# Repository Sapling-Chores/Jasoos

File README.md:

<div align = "center">

# Jasoos

</div>

This is compact keychain voice recorder (~~Not a Spy Gadget~~). This project uses an esp32 s3 with a sd card slot and a cam module that I wish to use in the upgraded version of this project. This project uses an INMP441 to record very good quality audio. Most interestingly, to on the device you have to enter a certain morse using tactile button. This project also uses a sleep mechanism that you can set in the code.

## Why I made this project?

I am a very big fan of crime documentories and shows that forces you to think. So I always thought, what can I do in a situation like a threat or a fight or an argument that could get you in trouble later. And yeah its simple just carry a voice recorder (for ethical use only) that can record audio whenever you want.

## Schematics:

## PCB:

# Cad

Snap fit cross section:

Snap fit female

snap fit male

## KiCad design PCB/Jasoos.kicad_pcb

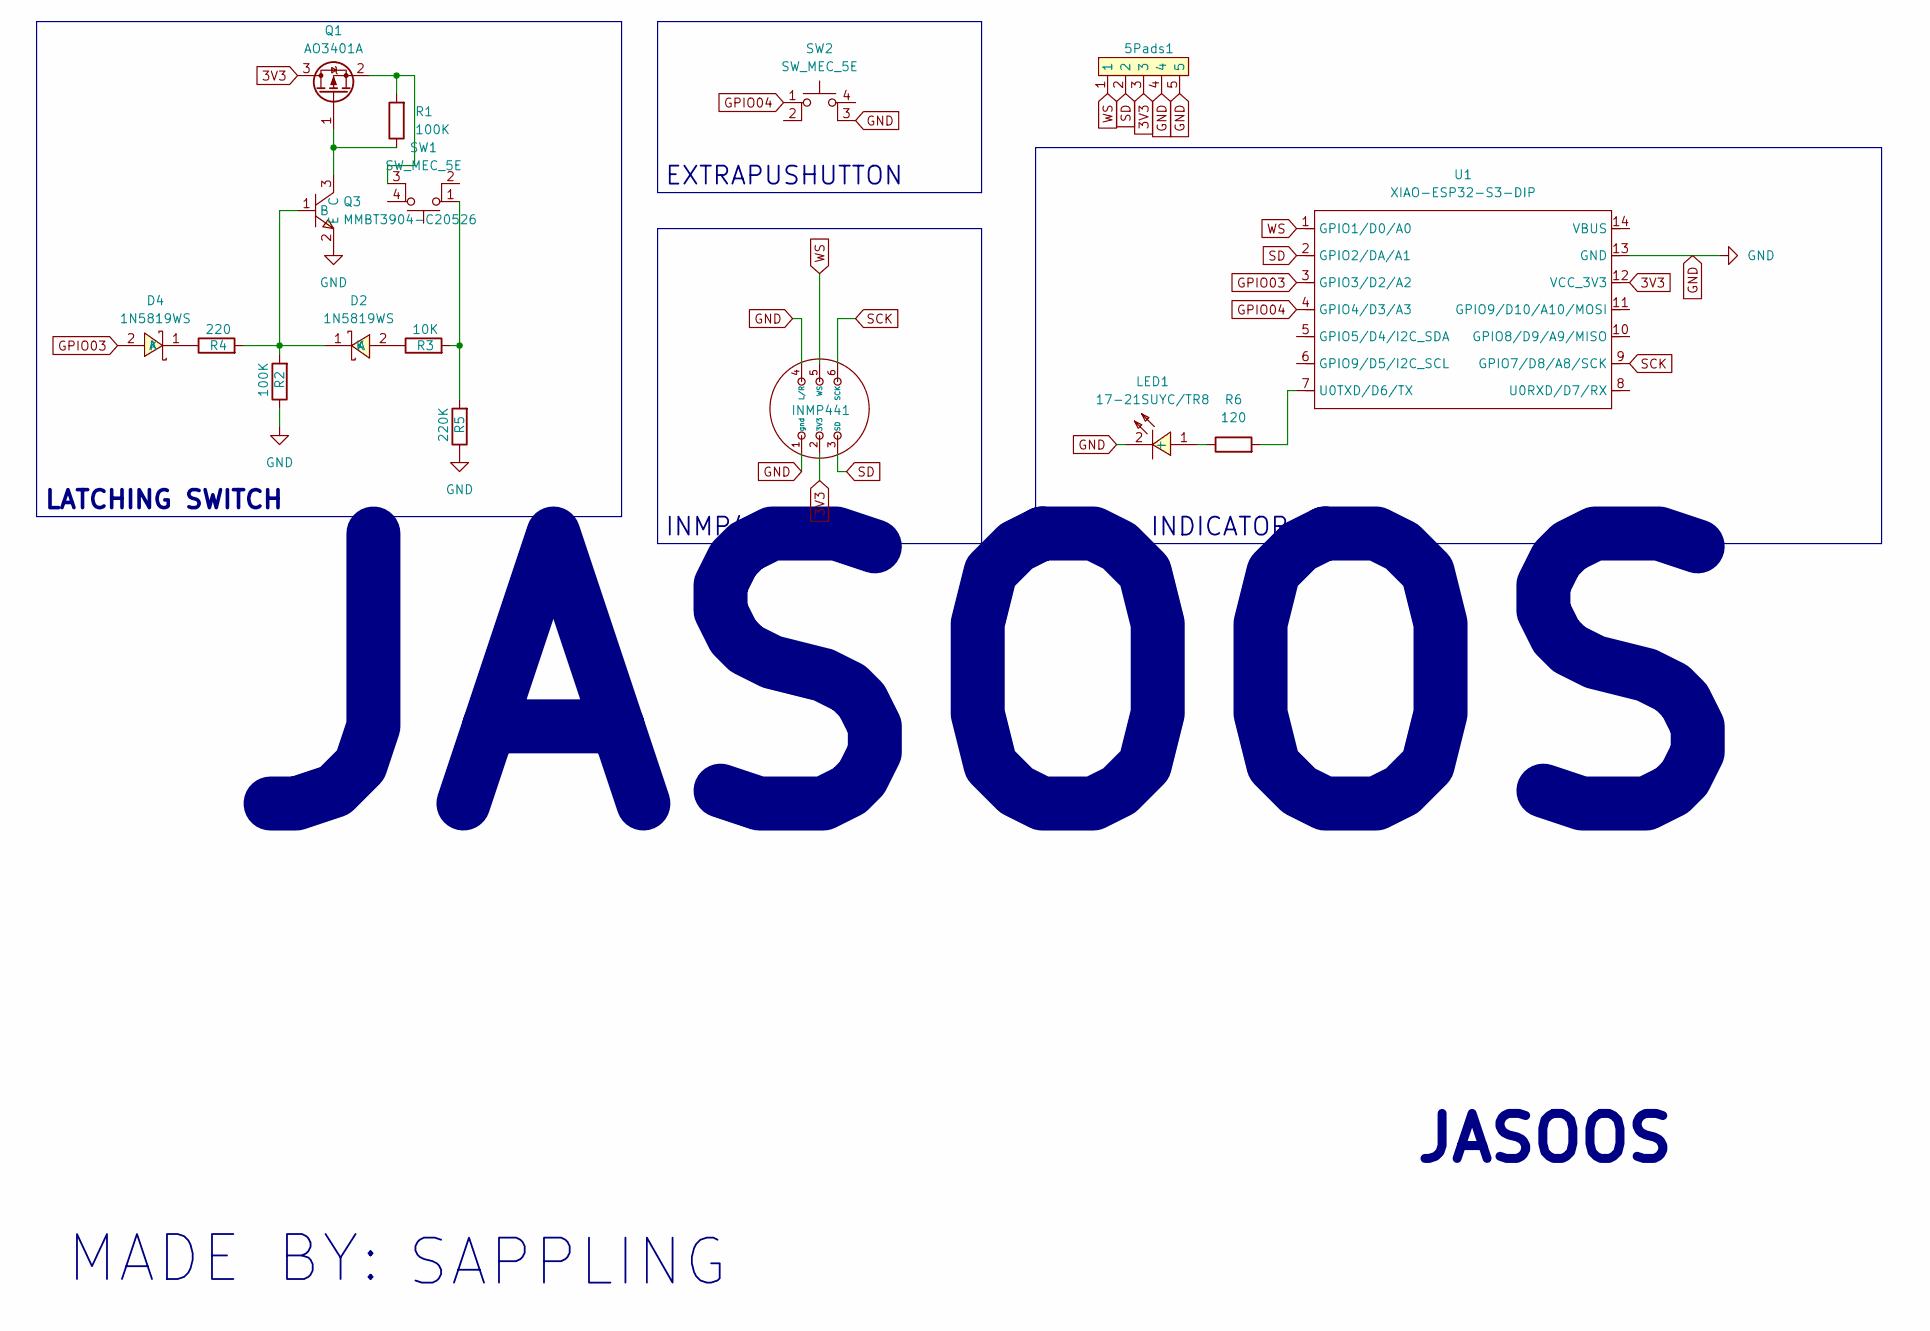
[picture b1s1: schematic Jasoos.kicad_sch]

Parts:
5Pads1: 5_PIN_PAD_1.6_W_2_H_0.8
D2, D4: 1N5819WS; SOD-323_L1.8-W1.3-LS2.5-RD; LCSC Part C191023
INMP441: INMP441
LED1: 17-21SUYC/TR8; LED0805-R-RD; LCSC Part C2296
Q1: AO3401A; SOT-23
Q3: MMBT3904-C20526; SOT-23-3_L2.9-W1.3-P1.90-LS2.4-BR; LCSC Part C20526
R1, R2: 100K; R0402
R3: 10K; R0402
R4: 220; R0402
R5: 220K; R0402
R6: 120; R0402
SW1: SW_MEC_5E; 2_PAD_1.6W_2H_0.8
SW2: SW_MEC_5E; 2_PAD_2W_1.6_0.8
U1: XIAO-ESP32-S3-DIP; XIAO-ESP32S3-DIP

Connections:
3V3: 5Pads1.3, INMP441.2 (3V3), Q1.3 (D), U1.12 (VCC_3V3)
GND: 5Pads1.4, 5Pads1.5, INMP441.1 (gnd), INMP441.4 (L/R), LED1.2 (-), Q3.2 (E), R2.1, R5.1, SW2.3 (K), U1.13 (GND)
GPIO03: D4.2 (A), U1.3 (GPIO3/D2/A2)
GPIO04: SW2.1, U1.4 (GPIO4/D3/A3)
unnamed: D2.2 (A), R3.1
unnamed: D2.1 (K), Q3.1 (B), R2.2, R4.2
unnamed: D4.1 (K), R4.1
unnamed: LED1.1 (+), R6.1
unnamed: Q1.1 (G), Q3.3 (C), R1.1
unnamed: Q1.2 (S), R1.2, SW1.3 (K)
unnamed: R3.2, R5.2, SW1.1
unnamed: R6.2, U1.7 (U0TXD/D6/TX)
SCK: INMP441.6 (SCK), U1.9 (GPIO7/D8/A8/SCK)
SD: 5Pads1.2, INMP441.3 (SD), U1.2 (GPIO2/DA/A1)
WS: 5Pads1.1, INMP441.5 (WS), U1.1 (GPIO1/D0/A0)

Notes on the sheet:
MADE BY:
SAPPLING
JASOOS
INMP441
EXTRAPUSHUTTON
MCU + INDICATOR_LED
LATCHING SWITCH

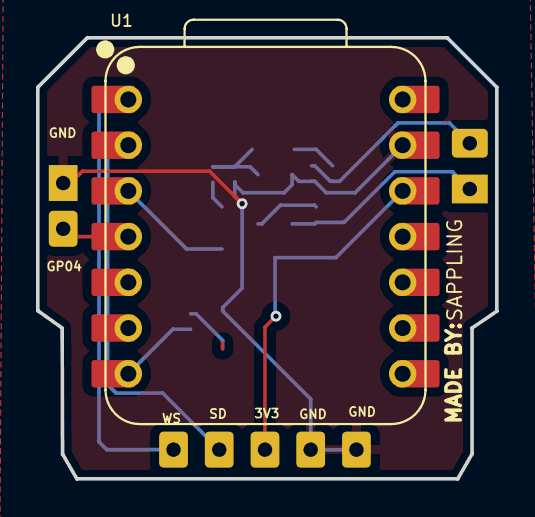
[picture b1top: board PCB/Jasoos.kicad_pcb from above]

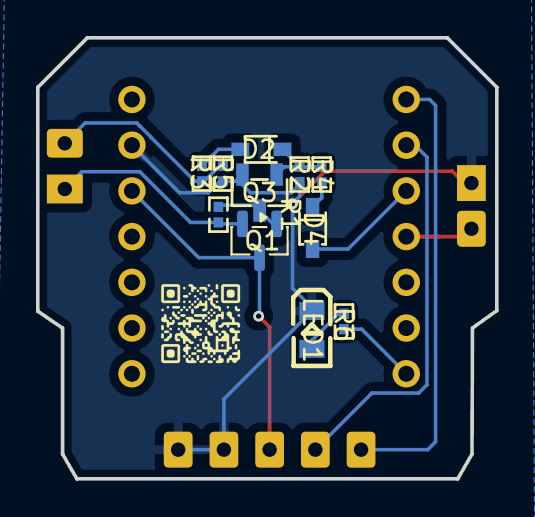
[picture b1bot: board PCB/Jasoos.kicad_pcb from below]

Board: 2 copper layers, 25.5 x 24.5 mm, 15 parts (12 on the bottom side), 14 nets.

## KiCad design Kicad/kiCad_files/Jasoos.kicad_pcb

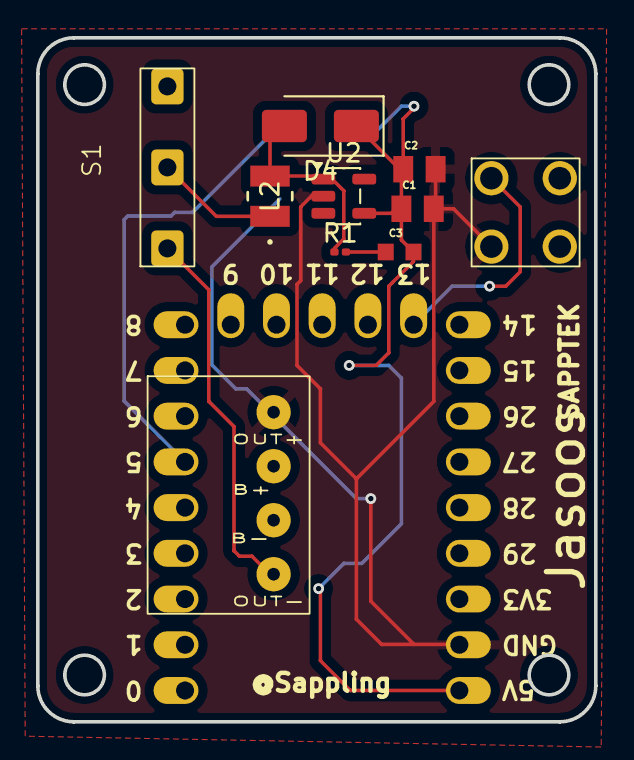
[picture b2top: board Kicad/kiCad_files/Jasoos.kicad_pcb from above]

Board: 2 copper layers, 31.0 x 38.0 mm, 12 parts (1 on the bottom side), 8 nets.

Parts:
C1, C2: 22 µF; CAPC2012X145N
C3: 120pF; CAPC1608X90N
D2: WS2812B; LED_WS2812B_PLCC4_5.0x5.0mm_P3.2mm
D4: SS34; D_SMA
L2: DFE252012F-2R2M=P2; IND_DFE252012_MUR
R1: 5; R_0201_0603Metric
S1: EG1218; Untitled
TP1: TP4056; Untitled
U1: RP2040_Zero
U2: TPS613222ADBV; SOT-23-5
U3: PUSHBUTTON; Untitled

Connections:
5V: C1.1, C2.1, C3.2, D2.1 (VDD), D4.1 (K), U1.23 (5V), U2.4 (VOUT)
GND: C1.2, C2.2, D2.3 (VSS), TP1.1 (OUT-), U1.22 (GND), U2.2 (GND), U3.3
LED DIN: D2.4 (DIN), U1.6 (5)
unnamed: C3.1, R1.2
unnamed: D4.2 (A), L2.2, R1.1, U2.1 (SW)
unnamed: L2.1, S1.2
unnamed: S1.1, TP1.4 (OUT+)
pushPin: U1.14 (13), U3.1

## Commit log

2026-02-09 Added Cad files and PCB files
2026-02-09 Rename Firmware.ino to Firmware.cpp
2026-03-05 Revise project overview and purpose in README
    Updated project description and added motivation for creation.
2026-03-05 Update LICENSE
2026-03-05 Create LICENCE
2026-03-05 Fix typo in project description
    Corrected a typo in the explanation of the project's purpose.
